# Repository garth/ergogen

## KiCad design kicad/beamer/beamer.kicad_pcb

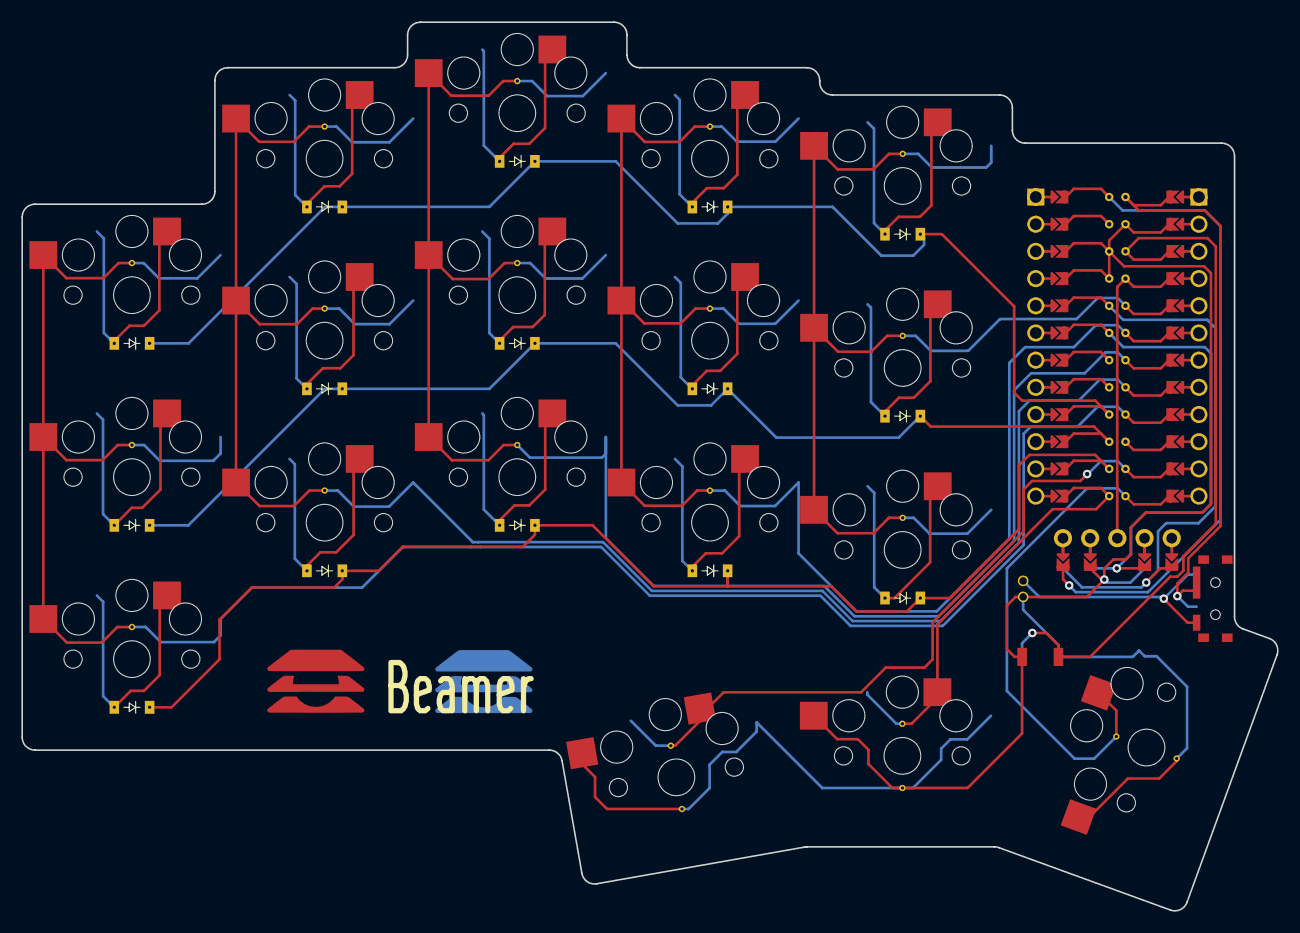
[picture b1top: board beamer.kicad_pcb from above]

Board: 2 copper layers, 117.3 x 83.0 mm, 15 parts (0 on the bottom side), 3 nets.

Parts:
D1, D2, D3, D4, D5, D6, D7, D8, D9, D10, D11, D12, D13, D14, D15: ComboDiode

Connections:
P6: D3.1, D6.1, D9.1, D12.1, D15.1
P7: D2.1, D5.1, D8.1, D11.1, D14.1
P8: D1.1, D4.1, D7.1, D10.1, D13.1

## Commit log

2022-12-29 Create the Beamer pcb
2022-12-29 Update logo and generate gerber files
2022-12-30 Final changes for printing
2022-12-30 Add missing drl files
